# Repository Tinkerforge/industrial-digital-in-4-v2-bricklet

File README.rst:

Industrial Digital In 4 Bricklet 2.0
====================================

This repository contains the firmware source code and the hardware design
files. The documentation generator configs can be found at
https://github.com/Tinkerforge/generators

Repository Content
------------------

software/:
 * examples/: Examples for all supported languages
 * build/: Compiled files
 * src/: Source code of firmware
 * Makefile: Makefile to build project

hardware/:
 * Contains KiCad project files and additionally schematics as PDF

datasheets/:
 * Contains datasheets for sensors and complex ICs that are used

Hardware
--------

The hardware is designed with the open source EDA Suite KiCad
(http://www.kicad.org). Before you are able to open the files,
you have to install the Tinkerforge kicad-libraries
(https://github.com/Tinkerforge/kicad-libraries). You can either clone
them directly in hardware/ or clone them in a separate folder and
symlink them into hardware/
(ln -s kicad_path/kicad-libraries project_path/hardware). After that you
can open the .pro file in hardware/ with KiCad and from there view and
modify the schematics and the PCB layout.

Software
--------

If you want to do your own Brick/Bricklet firmware development we highly
recommend that you use our build environment setup script and read the
tutorial (https://www.tinkerforge.com/en/doc/Tutorials/Tutorial_Build_Environment/Tutorial.html).

To compile the C code we recommend you to install the newest GNU Arm Embedded
Toolchain (https://launchpad.net/gcc-arm-embedded/+download).
You also need to install bricklib2 (https://github.com/Tinkerforge/bricklib2).

You can either clone it directly in software/src/ or clone it in a
separate folder and symlink it into software/src/
(ln -s bricklib_path/bricklib2 project_path/software/src/). Finally make sure to
have CMake installed (http://www.cmake.org/cmake/resources/software.html).

After that you can build the firmware by invoking make in software/.
The firmware (.zbin) can then be found in software/build/ and uploaded
with brickv (click button "Flashing" on start screen).

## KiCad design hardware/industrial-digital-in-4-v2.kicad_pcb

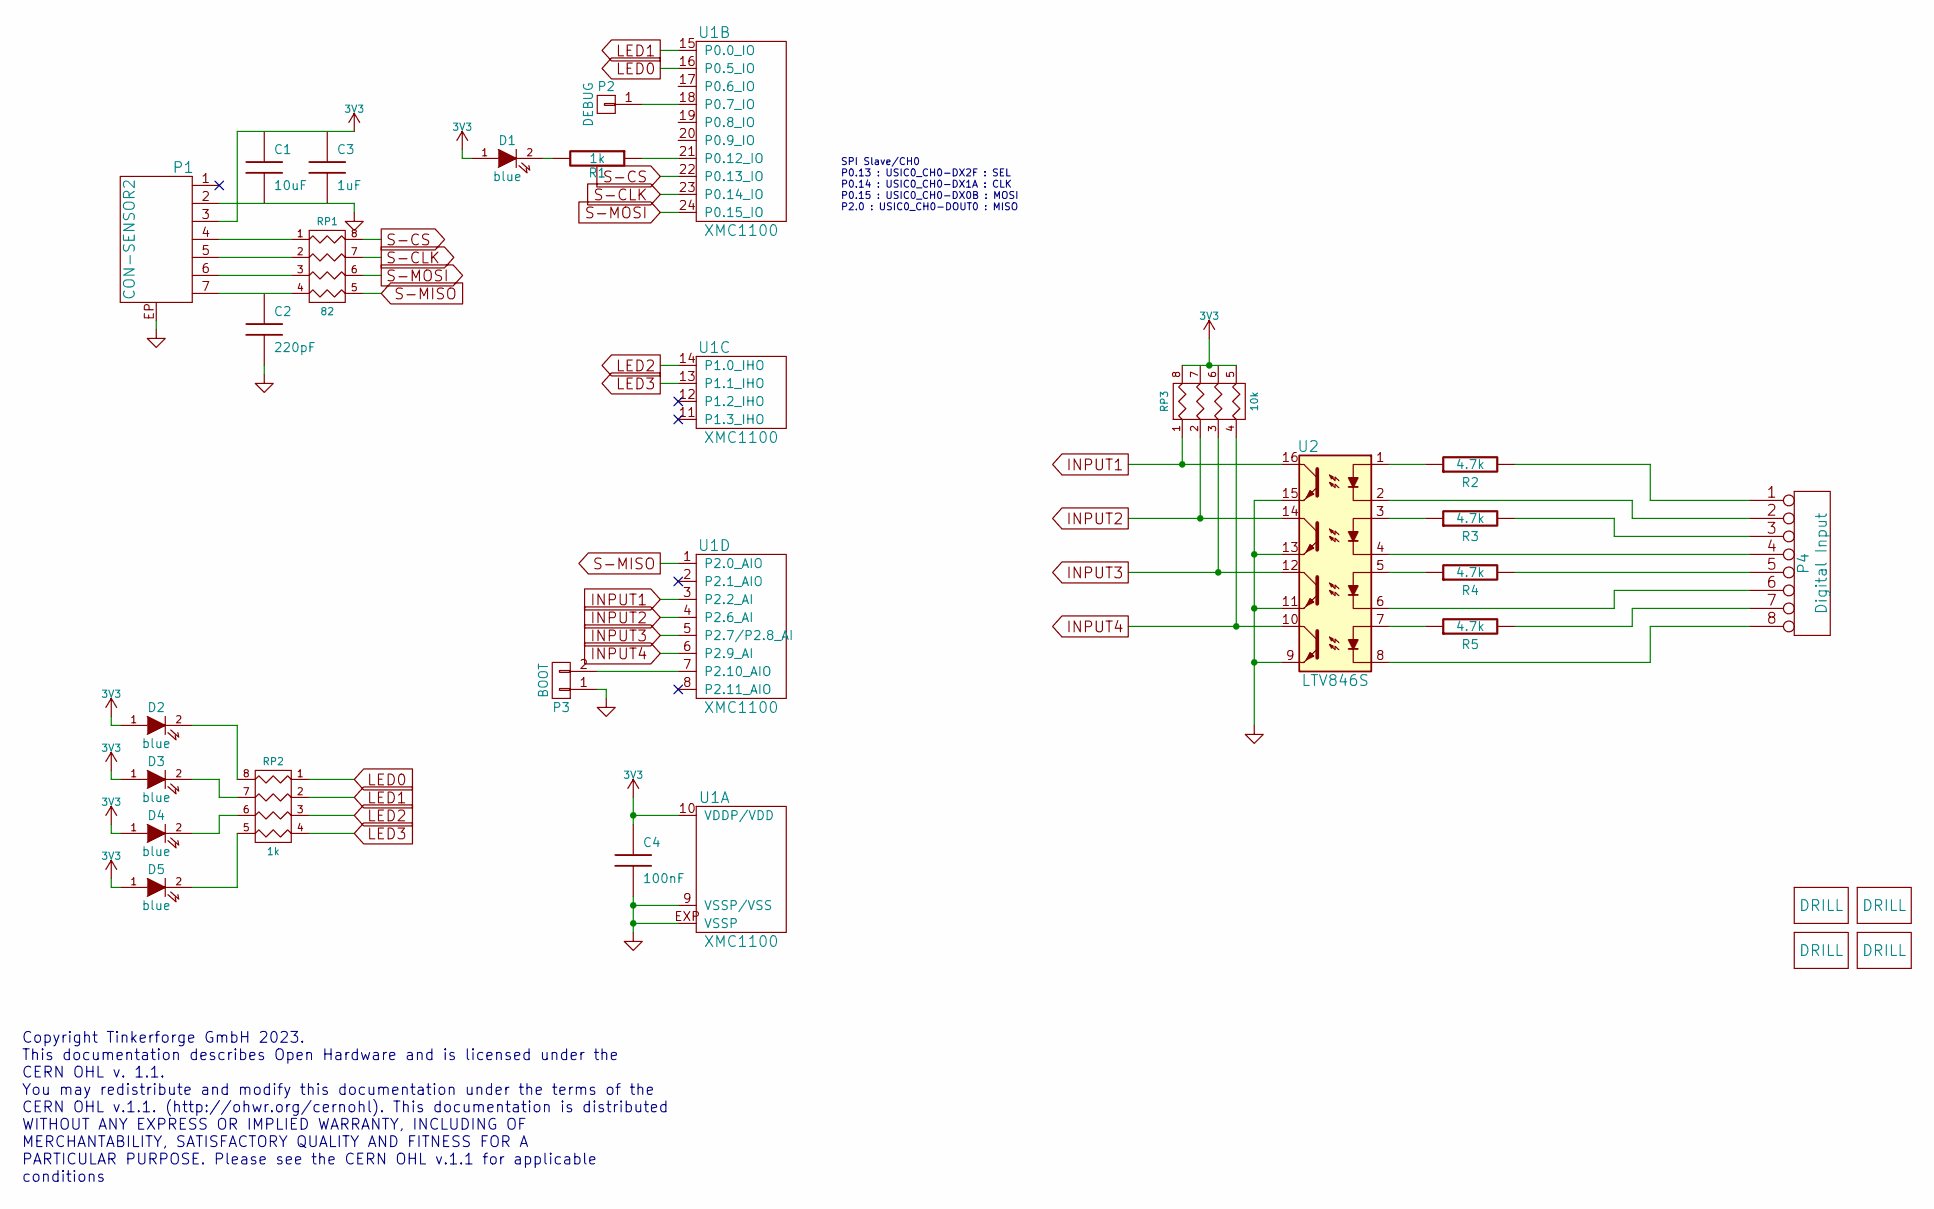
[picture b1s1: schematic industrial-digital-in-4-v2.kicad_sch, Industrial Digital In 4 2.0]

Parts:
C1: 10uF; C0805
C2: 220pF; C0402F
C3: 1uF; C0603F
C4: 100nF; C0603F
D1, D2, D3, D4, D5: blue; D0603F
P1: CON-SENSOR2
P2: DEBUG; DEBUG_PAD
P3: BOOT; SolderJumper
P4: Digital Input; OQ_8P
R1: 1k; R0603F
R2, R3, R4, R5: 4.7k; R1210
RP1: 82; 4X0402
RP2: 1k; 0603X4
RP3: 10k; 0603X4
U1: XMC1100; QFN24-4x4mm-0.5mm
U2: LTV846S; DIP-16
U3, U4, U5, U6: DRILL; DRILL_NP

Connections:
3V3: C1.1, C3.1, C4.1, D1.1 (A), D2.1 (A), D3.1 (A), D4.1 (A), D5.1 (A), P1.3, RP3.5 (R4), RP3.6 (R3), RP3.7 (R2), RP3.8 (R1), U1.10 (VDDP/VDD)
GND: C1.2, C2.2, C3.2, C4.2, P1.2, P1.EP, P3.1, U1.9 (VSSP/VSS), U1.EXP (VSSP), U2.9, U2.11, U2.13, U2.15
INPUT1: RP3.1, U1.3 (P2.2_AI), U2.16
INPUT2: RP3.2, U1.4 (P2.6_AI), U2.14
INPUT3: RP3.3, U1.5 (P2.7/P2.8_AI), U2.12
INPUT4: RP3.4, U1.6 (P2.9_AI), U2.10
LED0: RP2.1, U1.16 (P0.5_IO)
LED1: RP2.2, U1.15 (P0.0_IO)
LED2: RP2.3, U1.14 (P1.0_IHO)
LED3: RP2.4, U1.13 (P1.1_IHO)
unnamed: D1.2 (K), R1.2
unnamed: D2.2 (K), RP2.8 (R1)
unnamed: D3.2 (K), RP2.7 (R2)
unnamed: D4.2 (K), RP2.6 (R3)
unnamed: D5.2 (K), RP2.5 (R4)
unnamed: P1.4, RP1.1
unnamed: P1.5, RP1.2
unnamed: P1.6, RP1.3
unnamed: P2.1, U1.18 (P0.7_IO)
unnamed: P3.2, U1.7 (P2.10_AIO)
unnamed: P4.1, R2.2
unnamed: P4.2, U2.2
unnamed: P4.3, R3.2
unnamed: P4.4, U2.4
unnamed: P4.5, R4.2
unnamed: P4.6, U2.6
unnamed: P4.7, R5.2
unnamed: P4.8, U2.8
unnamed: R1.1, U1.21 (P0.12_IO)
unnamed: R2.1, U2.1
unnamed: R3.1, U2.3
unnamed: R4.1, U2.5
unnamed: R5.1, U2.7
S-CLK: RP1.7 (R2), U1.23 (P0.14_IO)
S-CS: RP1.8 (R1), U1.22 (P0.13_IO)
S-MISO: RP1.5 (R4), U1.1 (P2.0_AIO)
S-MOSI: RP1.6 (R3), U1.24 (P0.15_IO)

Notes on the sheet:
SPI Slave/CH0 P0.13 : USIC0_CH0-DX2F : SEL P0.14 : USIC0_CH0-DX1A : CLK P0.15 : USIC0_CH0-DX0B : MOSI P2.0 : USIC0_CH0-DOUT0 : MISO
Copyright Tinkerforge GmbH 2023. This documentation describes Open Hardware and is licensed under the CERN OHL v. 1.1. You may redistribute and modify this documentation under the terms of the CERN OHL v.1.1. (http://ohwr.org/cernohl). This documentation is distributed WITHOUT ANY EXPRESS OR IMPLIE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

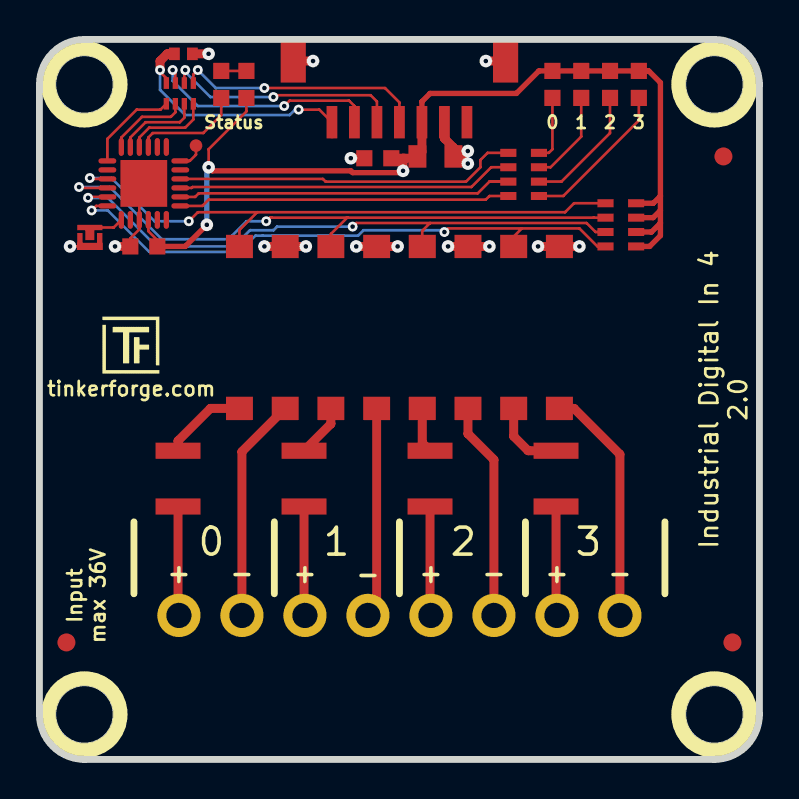
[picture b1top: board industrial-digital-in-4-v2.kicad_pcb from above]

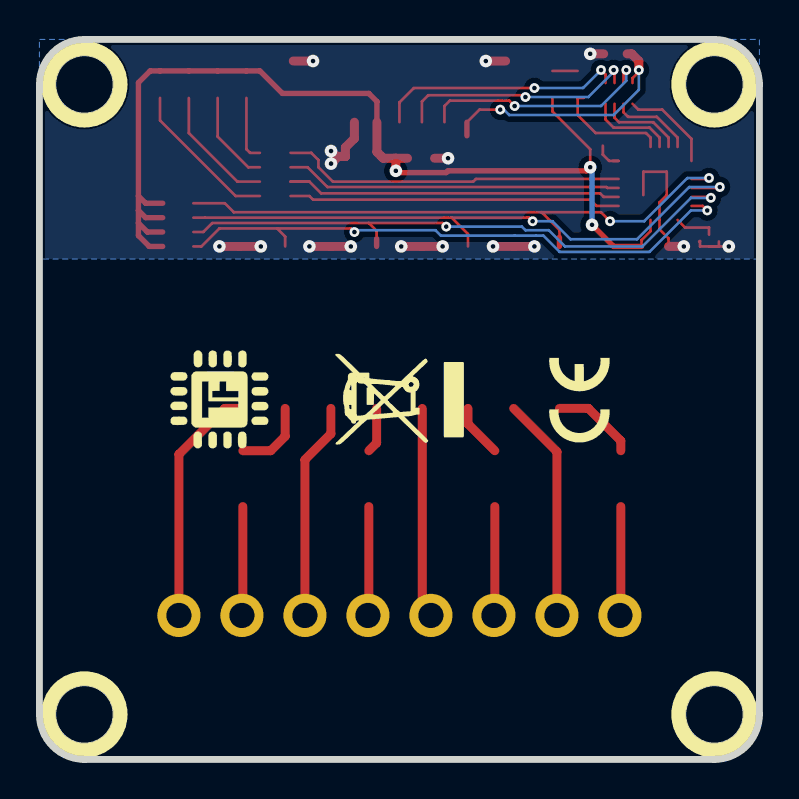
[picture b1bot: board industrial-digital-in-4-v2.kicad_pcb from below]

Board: 2 copper layers, 40.0 x 40.0 mm, 32 parts (2 on the bottom side), 38 nets.

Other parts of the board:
Fiducial_Mark: VAL**; Fiducial_Mark
Fiducial_Mark#2, Fiducial_Mark#3: VAL**; Fiducial_Mark
VAL: CE_5mm
VAL#2: WEEE_7mm

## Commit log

2017-12-08 add first hardware prototype
2017-12-08 change led position
2017-12-08 add missing text informations
2018-02-07 fix spi slave interface pins
2018-02-20 Add .gitignore
2018-02-20 Cleanup KiCad libraries config
    Ensure LibDir=kicad-libraries and LibName1=tinkerforge.
    Remove special library.
2018-03-15 change weee symbol position
2018-03-15 fix logo positions
2018-03-16 fix led text size
2018-03-27 specify processor
2018-04-11 Firmware implementation
2018-04-11 Add tests
2018-04-12 Disable logging
2018-04-12 Remove unused source includes
2018-04-16 Add 3d model (*.FCStd & *.step)
2018-05-02 Rename info LED to channel LED
2018-05-04 Rename files
2018-05-04 Add schematic PDF
2018-05-28 Change LED color
2018-05-28 Fix schematic
2018-05-29 Adapt to Bindings API naming change from input-value to just value
2018-05-29 Remove unnecessary get-selected-value function
2018-06-07 Update changelog for initial release
2018-06-18 Change capacitor footprint(s) to C0402F
2018-06-28 Fix readme
2018-07-11 Add Makefile with docker support
2018-07-11 Remove obsolete generate_makefile scripts
2018-07-11 Update directory structure and build instructions
2018-09-13 Add auto-generated examples
2018-09-14 examples: Fix typos
2018-09-14 examples: Use common callback config pattern
2018-09-27 examples: Fix type errors
2018-09-27 examples: Rename Input to Simple
2018-09-27 Add simple LabVIEW example
2018-10-04 Increase version for new release (changes in bricklib2)
2018-10-04 Add rev to changelog
2018-10-23 fix via diameter, drc
2018-11-06 Add rust examples
2018-11-07 rust: Accept host names for ip connection, fix naming inconsistencies
2018-11-07 rust: Rename callback receivers.
2018-12-14 Add go examples.
2018-12-18 go: Change import path.
2018-12-18 go: Change import path again.
2018-12-20 Fix constant handling in examples.
2018-12-20 rust: Reformat examples.
2019-01-24 mqtt: Add examples.
2019-01-24 mqtt: Fix example header.
2019-01-24 mqtt: Remove executable bit in example permissions.
2019-01-24 go: Minor example fixes.
2019-01-24 mqtt: Minor example fixes.
2019-01-29 rust: Fix unused loop index.
2019-03-25 mqtt: Fix example whitespace.
2019-03-28 mqtt: Fix whitespace.
2019-08-22 c: Adapt to bindings changes
2020-01-13 examples: Use python3 input instead of python2 raw_input.
2020-01-13 examples: mqtt: Remove trailing whitespace.
2020-02-26 drc and fixed board outline
2020-03-16 Whitespace
2020-03-23 mqtt: Update for loop style
2020-04-07 examples: rust: Always block when calling bindings functions.
2020-08-19 Add uc examples.
2020-08-25 uc: Fix whitespace
2020-08-27 uc: Fix warnings.
2020-08-31 uc: Use fixed-with placeholders in format strings.
2020-09-02 uc: Add example driver note.
2020-10-16 Simplify implementation (no functional changes)
    This new implementation should behave exactly like the old one,
    but with less flash usage. We need some more flash for the new
    Wiegand API.
2020-10-19 Add support for new Wiegand API
2020-10-21 Fix copy+paste error in callback implementation
2020-10-21 Save old value and time for proper callback handling
2020-10-22 wiegand: Add C tests
2020-10-22 wiegand: Fine-tune tests
2020-10-22 Disable debug logging
2020-10-22 wiegand: Move C bindings to subdirectory
2021-01-12 wiegand: Add Java tests
2021-01-12 Remove executable mode
2021-05-06 mathematica: Fix broken syntax
2021-10-25 Update KiCad link
    https://www.kicad.org/blog/2021/10/Avoid-links-to-former-kicad-domain/
2022-04-19 examples: uc: Rename TF_HalContext to TF_HAL.
2022-04-27 uc: Adapt to bindings changes
2022-05-10 go: Fix format string
2022-07-06 Add license files.
2023-01-30 move to kicad 6
2023-01-30 Data Cleanup
2025-10-04 Fix compatibility with new Docker build image (GCC 14.2.1)

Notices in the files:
hardware/industrial-digital-in-4-v2.kicad_pcb:
Licensed under CERN OHL v.1.1
Copyright (©) 2023, B.Nordmeyer
